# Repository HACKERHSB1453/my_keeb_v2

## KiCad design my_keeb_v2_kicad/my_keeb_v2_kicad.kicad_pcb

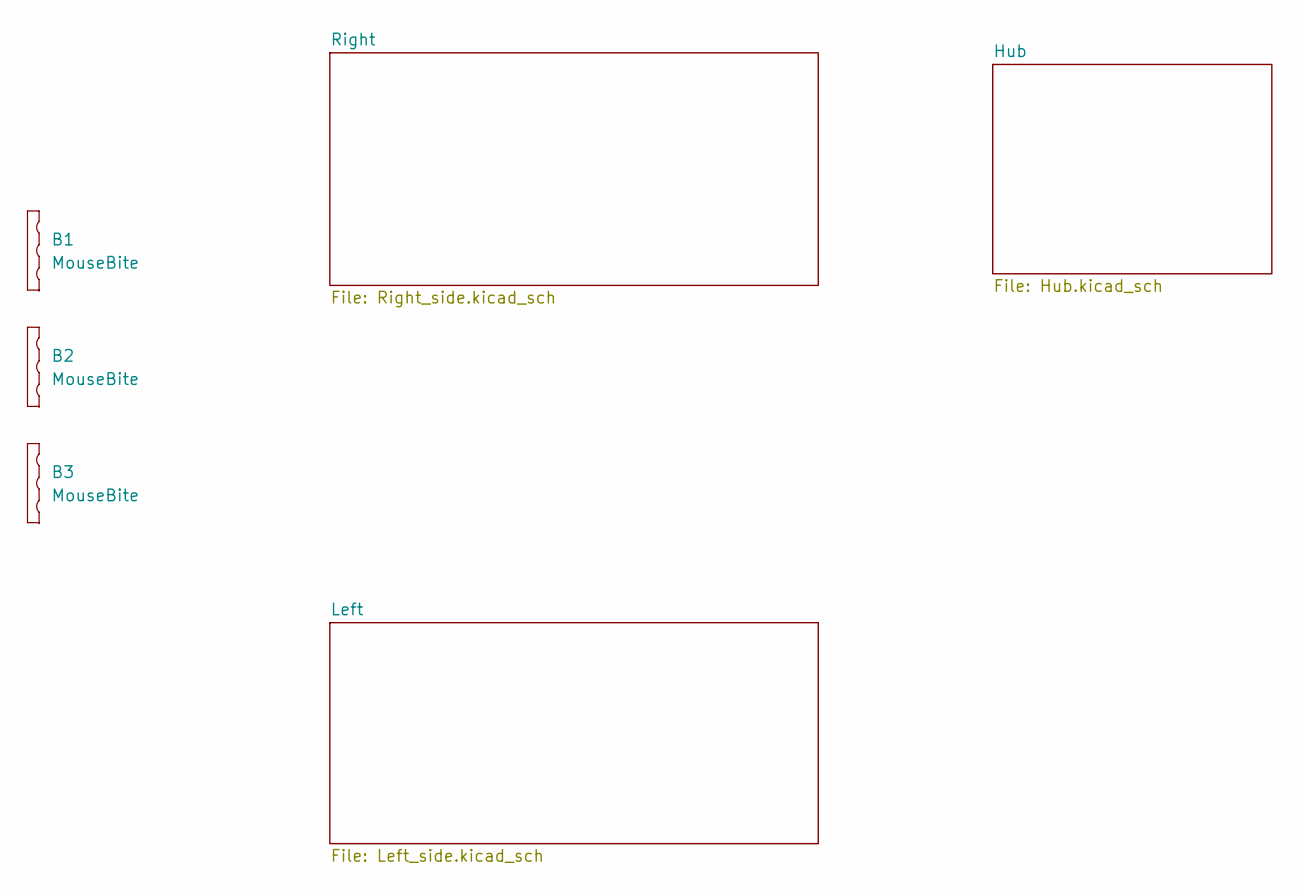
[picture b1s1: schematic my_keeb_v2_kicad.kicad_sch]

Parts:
B1, B2, B3: MouseBite; mousebites_2mm

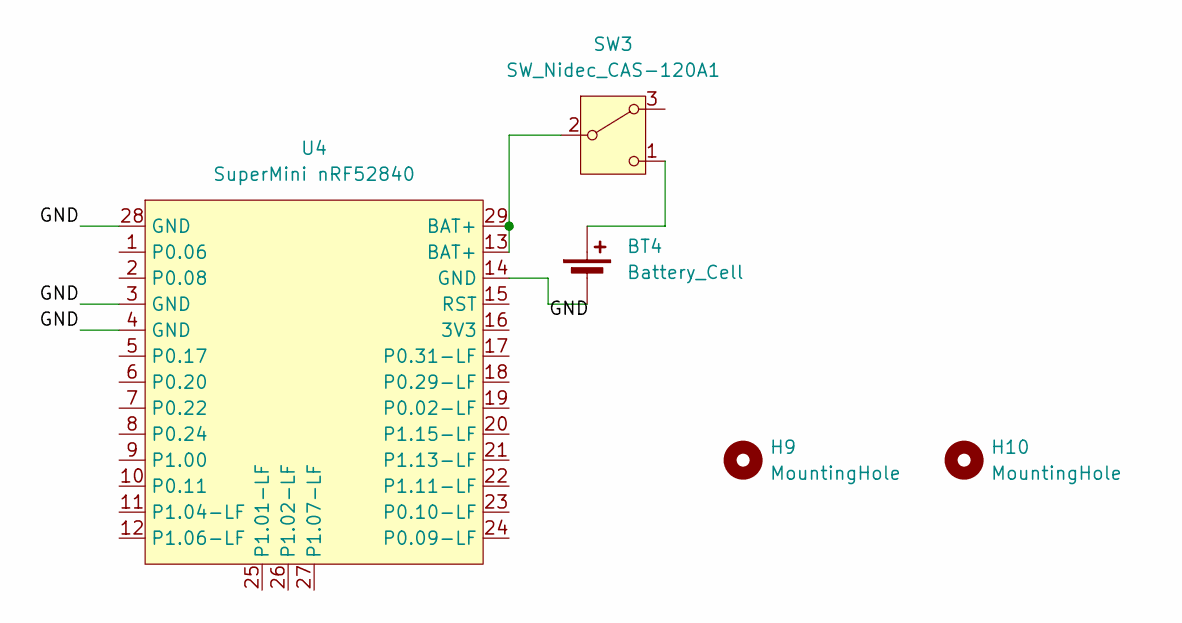
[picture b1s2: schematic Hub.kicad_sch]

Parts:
BT4: Battery_Cell; JST_PH_S2B-PH-SM4-TB_1x02-1MP_P2.00mm_Horizontal
H9, H10: MountingHole; MountingHole_2.2mm_M2
SW3: SW_Nidec_CAS-120A1; SW_SPDT_PCM12
U4: SuperMini nRF52840; SuperMini_nRF52840_AH_USBup

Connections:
/Hub/GND: BT4.2 (-), U4.3 (GND), U4.4 (GND), U4.14 (GND), U4.28 (GND)
unnamed: BT4.1 (+), SW3.1 (C)
unnamed: SW3.2 (B), U4.13 (BAT+), U4.29 (BAT+)

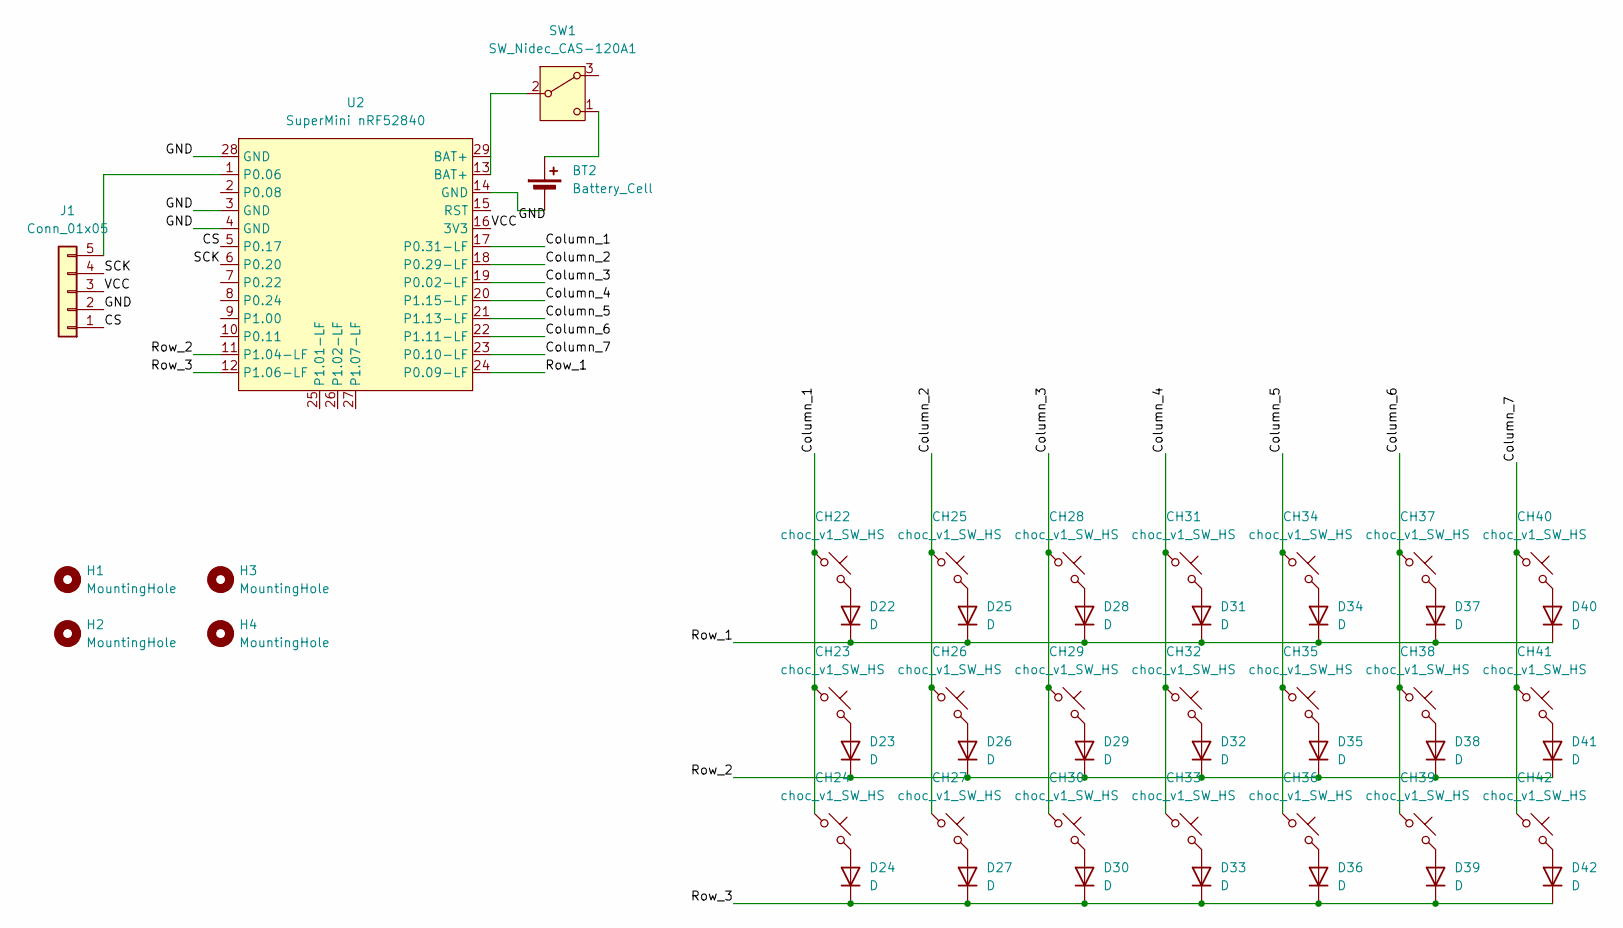
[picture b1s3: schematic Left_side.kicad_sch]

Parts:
BT2: Battery_Cell; JST_PH_S2B-PH-SM4-TB_1x02-1MP_P2.00mm_Horizontal
CH22, CH23, CH24, CH25, CH26, CH27, CH28, CH29, CH30, CH31, CH32, CH33, CH34, CH35, CH36, CH37, CH38, CH39, CH40, CH41, CH42: choc_v1_SW_HS; SW_choc_v1v2_HS_1u
D22, D23, D24, D25, D26, D27, D28, D29, D30, D31, D32, D33, D34, D35, D36, D37, D38, D39, D40, D41, D42: D; D_SOD-123
H1, H2, H3, H4: MountingHole; MountingHole_2.2mm_M2
J1: Conn_01x05; PinSocket_1x05_P2.54mm_Vertical
SW1: SW_Nidec_CAS-120A1; SW_SPDT_PCM12
U2: SuperMini nRF52840; SuperMini_nRF52840_AH_USBup

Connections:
/Left/CS: J1.1, U2.5 (P0.17)
/Left/Column_1: CH22.1, CH23.1, CH24.1, U2.17 (P0.31-LF)
/Left/Column_2: CH25.1, CH26.1, CH27.1, U2.18 (P0.29-LF)
/Left/Column_3: CH28.1, CH29.1, CH30.1, U2.19 (P0.02-LF)
/Left/Column_4: CH31.1, CH32.1, CH33.1, U2.20 (P1.15-LF)
/Left/Column_5: CH34.1, CH35.1, CH36.1, U2.21 (P1.13-LF)
/Left/Column_6: CH37.1, CH38.1, CH39.1, U2.22 (P1.11-LF)
/Left/Column_7: CH40.1, CH41.1, CH42.1, U2.23 (P0.10-LF)
/Left/GND: BT2.2 (-), J1.2, U2.3 (GND), U2.4 (GND), U2.14 (GND), U2.28 (GND)
/Left/Row_1: D22.1 (K), D25.1 (K), D28.1 (K), D31.1 (K), D34.1 (K), D37.1 (K), D40.1 (K), U2.24 (P0.09-LF)
/Left/Row_2: D23.1 (K), D26.1 (K), D29.1 (K), D32.1 (K), D35.1 (K), D38.1 (K), D41.1 (K), U2.11 (P1.04-LF)
/Left/Row_3: D24.1 (K), D27.1 (K), D30.1 (K), D33.1 (K), D36.1 (K), D39.1 (K), D42.1 (K), U2.12 (P1.06-LF)
/Left/SCK: J1.4, U2.6 (P0.20)
/Left/VCC: J1.3, U2.16 (3V3)
unnamed: BT2.1 (+), SW1.1 (C)
unnamed: CH22.2, D22.2 (A)
unnamed: CH23.2, D23.2 (A)
unnamed: CH24.2, D24.2 (A)
unnamed: CH25.2, D25.2 (A)
unnamed: CH26.2, D26.2 (A)
unnamed: CH27.2, D27.2 (A)
unnamed: CH28.2, D28.2 (A)
unnamed: CH29.2, D29.2 (A)
unnamed: CH30.2, D30.2 (A)
unnamed: CH31.2, D31.2 (A)
unnamed: CH32.2, D32.2 (A)
unnamed: CH33.2, D33.2 (A)
unnamed: CH34.2, D34.2 (A)
unnamed: CH35.2, D35.2 (A)
unnamed: CH36.2, D36.2 (A)
unnamed: CH37.2, D37.2 (A)
unnamed: CH38.2, D38.2 (A)
unnamed: CH39.2, D39.2 (A)
unnamed: CH40.2, D40.2 (A)
unnamed: CH41.2, D41.2 (A)
unnamed: CH42.2, D42.2 (A)
unnamed: J1.5, U2.1 (P0.06)
unnamed: SW1.2 (B), U2.13 (BAT+), U2.29 (BAT+)

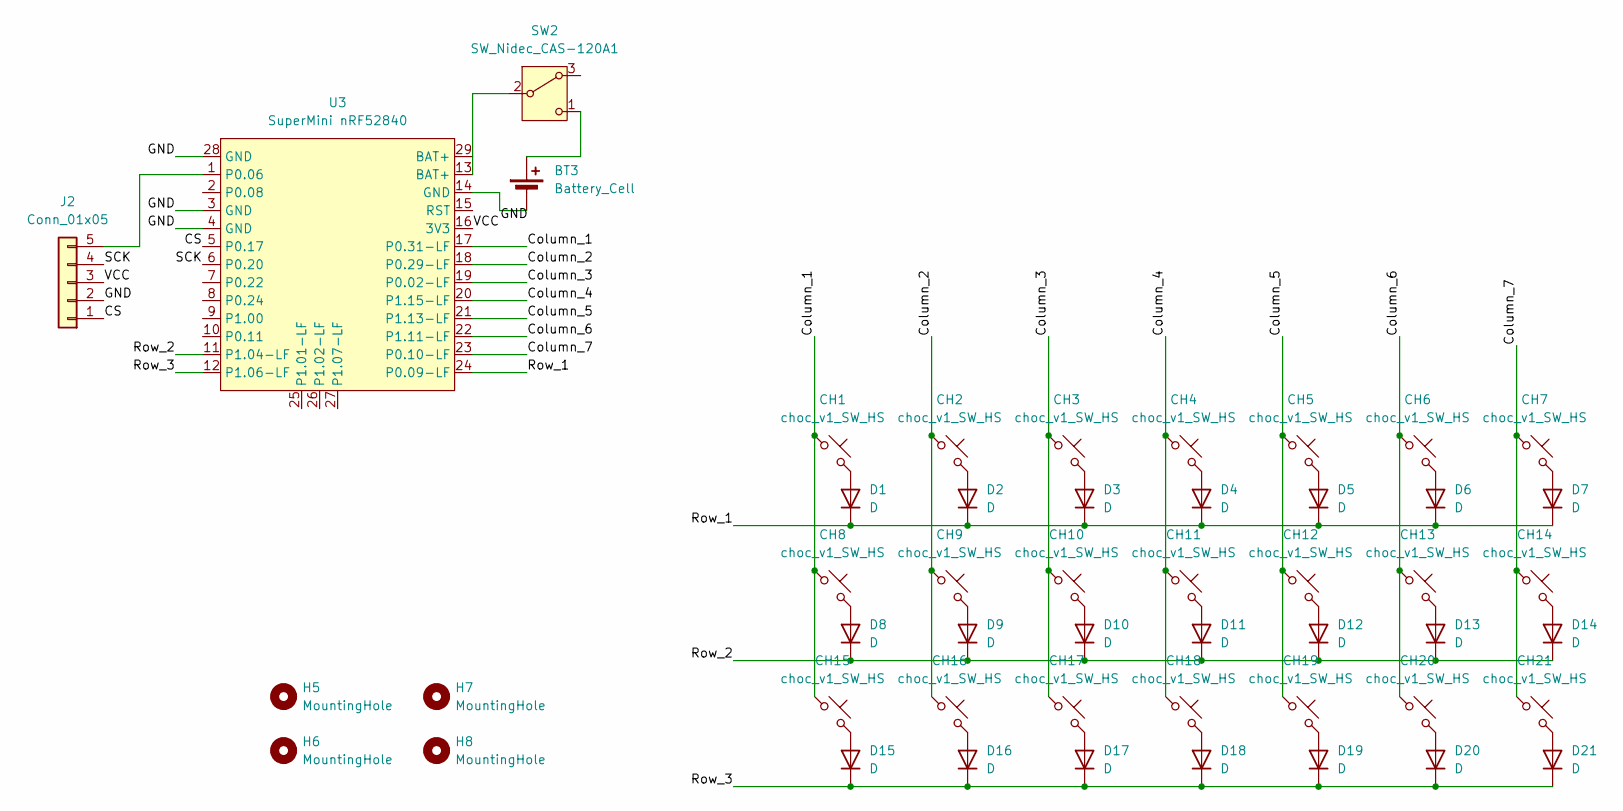
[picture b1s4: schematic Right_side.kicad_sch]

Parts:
BT3: Battery_Cell; JST_PH_S2B-PH-SM4-TB_1x02-1MP_P2.00mm_Horizontal
CH1, CH2, CH3, CH4, CH5, CH6, CH7, CH8, CH9, CH10, CH11, CH12, CH13, CH14, CH15, CH16, CH17, CH18, CH19, CH20, CH21: choc_v1_SW_HS; SW_choc_v1v2_HS_1u
D1, D2, D3, D4, D5, D6, D7, D8, D9, D10, D11, D12, D13, D14, D15, D16, D17, D18, D19, D20, D21: D; D_SOD-123
H5, H6, H7, H8: MountingHole; MountingHole_2.2mm_M2
J2: Conn_01x05; PinSocket_1x05_P2.54mm_Vertical
SW2: SW_Nidec_CAS-120A1; SW_SPDT_PCM12
U3: SuperMini nRF52840; SuperMini_nRF52840_AH_USBup

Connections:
/Right/CS: J2.1, U3.5 (P0.17)
/Right/Column_1: CH1.1, CH8.1, CH15.1, U3.17 (P0.31-LF)
/Right/Column_2: CH2.1, CH9.1, CH16.1, U3.18 (P0.29-LF)
/Right/Column_3: CH3.1, CH10.1, CH17.1, U3.19 (P0.02-LF)
/Right/Column_4: CH4.1, CH11.1, CH18.1, U3.20 (P1.15-LF)
/Right/Column_5: CH5.1, CH12.1, CH19.1, U3.21 (P1.13-LF)
/Right/Column_6: CH6.1, CH13.1, CH20.1, U3.22 (P1.11-LF)
/Right/Column_7: CH7.1, CH14.1, CH21.1, U3.23 (P0.10-LF)
/Right/GND: BT3.2 (-), J2.2, U3.3 (GND), U3.4 (GND), U3.14 (GND), U3.28 (GND)
/Right/Row_1: D1.1 (K), D2.1 (K), D3.1 (K), D4.1 (K), D5.1 (K), D6.1 (K), D7.1 (K), U3.24 (P0.09-LF)
/Right/Row_2: D8.1 (K), D9.1 (K), D10.1 (K), D11.1 (K), D12.1 (K), D13.1 (K), D14.1 (K), U3.11 (P1.04-LF)
/Right/Row_3: D15.1 (K), D16.1 (K), D17.1 (K), D18.1 (K), D19.1 (K), D20.1 (K), D21.1 (K), U3.12 (P1.06-LF)
/Right/SCK: J2.4, U3.6 (P0.20)
/Right/VCC: J2.3, U3.16 (3V3)
unnamed: BT3.1 (+), SW2.1 (C)
unnamed: CH1.2, D1.2 (A)
unnamed: CH2.2, D2.2 (A)
unnamed: CH3.2, D3.2 (A)
unnamed: CH4.2, D4.2 (A)
unnamed: CH5.2, D5.2 (A)
unnamed: CH6.2, D6.2 (A)
unnamed: CH7.2, D7.2 (A)
unnamed: CH8.2, D8.2 (A)
unnamed: CH9.2, D9.2 (A)
unnamed: CH10.2, D10.2 (A)
unnamed: CH11.2, D11.2 (A)
unnamed: CH12.2, D12.2 (A)
unnamed: CH13.2, D13.2 (A)
unnamed: CH14.2, D14.2 (A)
unnamed: CH15.2, D15.2 (A)
unnamed: CH16.2, D16.2 (A)
unnamed: CH17.2, D17.2 (A)
unnamed: CH18.2, D18.2 (A)
unnamed: CH19.2, D19.2 (A)
unnamed: CH20.2, D20.2 (A)
unnamed: CH21.2, D21.2 (A)
unnamed: J2.5, U3.1 (P0.06)
unnamed: SW2.2 (B), U3.13 (BAT+), U3.29 (BAT+)

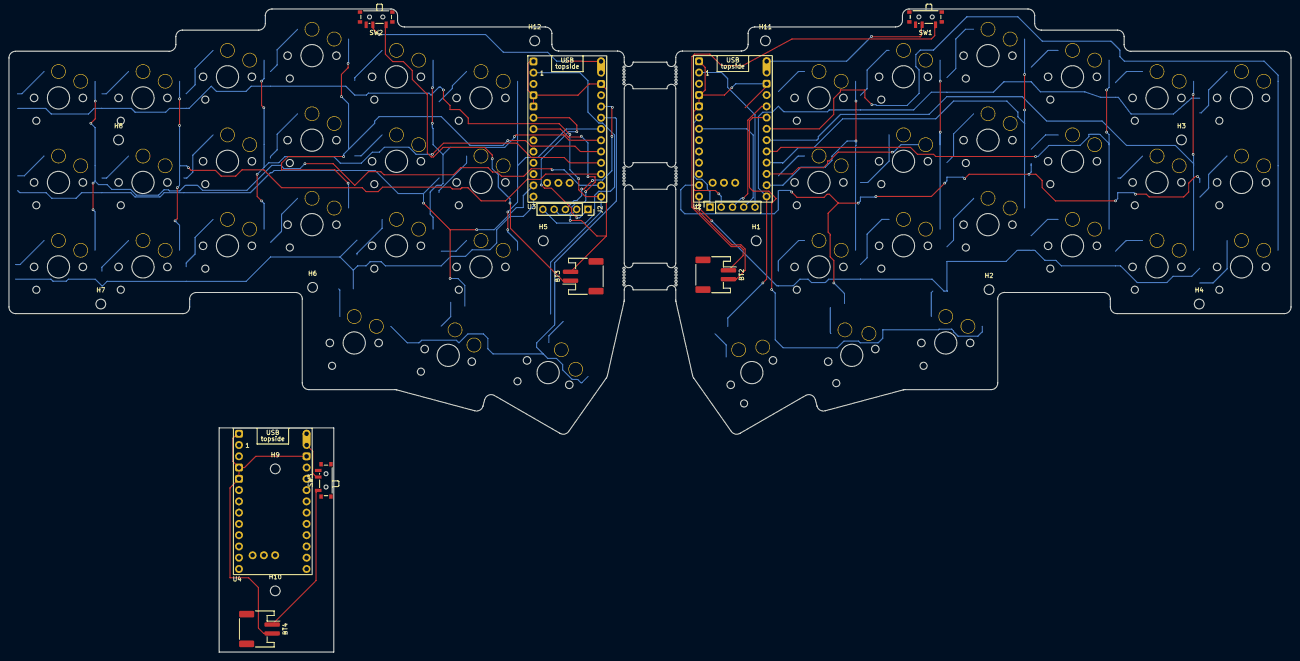
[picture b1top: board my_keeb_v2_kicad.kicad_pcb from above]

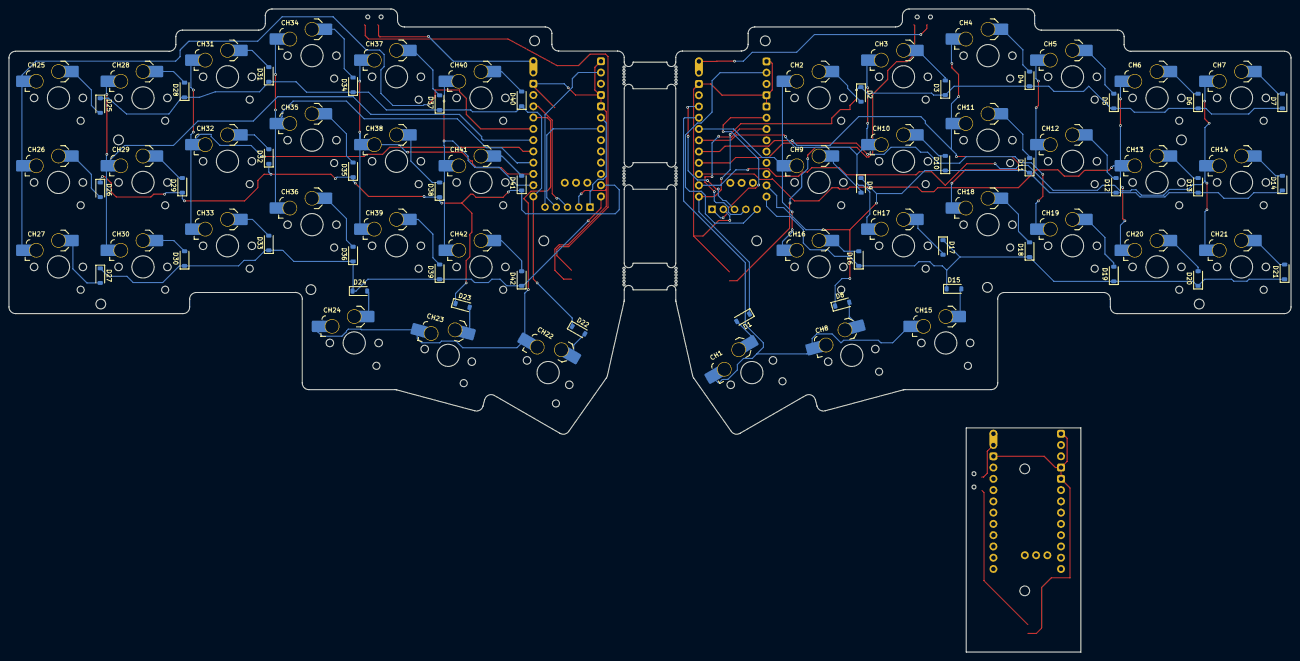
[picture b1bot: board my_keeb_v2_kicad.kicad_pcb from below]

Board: 2 copper layers, 289.0 x 95.9 mm, 113 parts (84 on the bottom side), 79 nets.

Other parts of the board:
B4, B5, B6: MouseBite; mousebites_2mm
H11, H12: MountingHole; MountingHole_2.2mm_M2
